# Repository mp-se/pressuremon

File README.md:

# Pressure Monitor for Beer Brewing

PressureMon is a device for measuring pressure in storage or during fermentation.  

It supports ESP32s2 mini, ESP32s3 mini, ESP32c3 mini, ESP32c3 pico and pico and I2C compatible pressure sensors, currently the brand XIDIBEI is supported which has a good range of encapsulated sensors.

Flashing can be done using https://www.gravitymon.com/flasher/index.html which also will help with wifi setup.

Documentation and flashing instructions are available on the [GravityMon PressureMon project page](https://gravitymon.com/project-pressuremon.html)

PCB design is located [here](https://github.com/mp-se/pcb-designs/) 

3D models for a case can be found in the 3d directory on github.

If you want to support my work you can do that through these options

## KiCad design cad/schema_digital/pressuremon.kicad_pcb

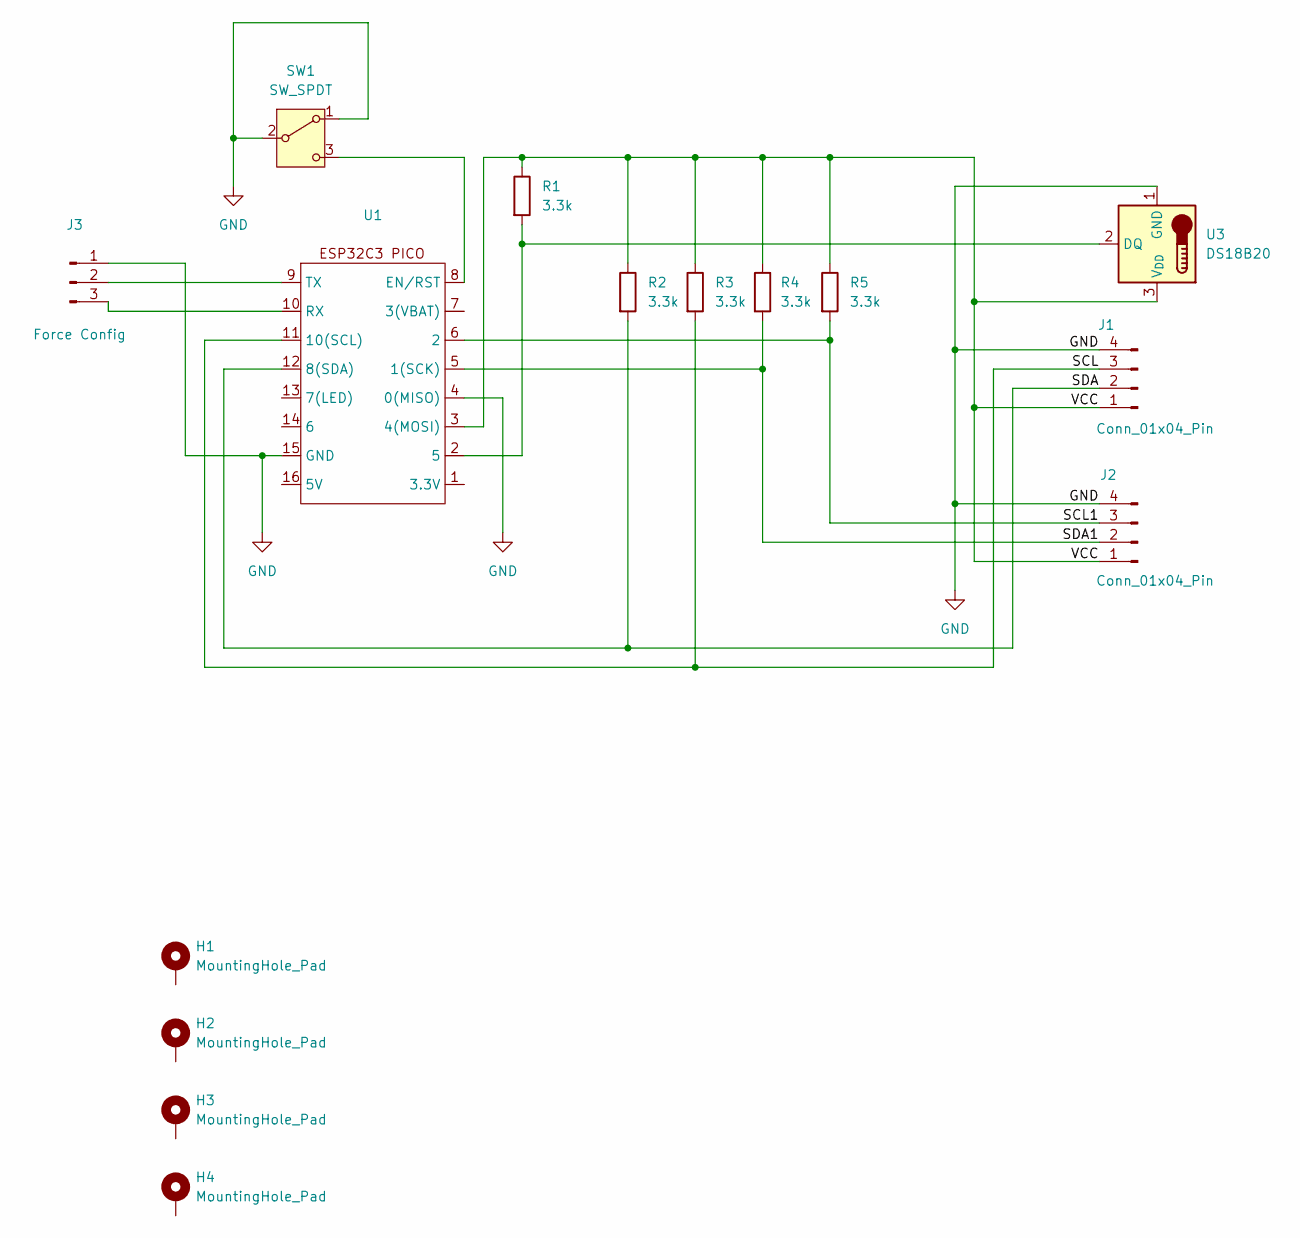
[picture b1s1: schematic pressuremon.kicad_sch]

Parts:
H1, H2, H3, H4: MountingHole_Pad; MountingHole_2.2mm_M2_ISO7380_Pad
J1, J2: Conn_01x04_Pin; PinHeader_1x04_P2.54mm_Vertical
J3: Force Config; PinHeader_1x03_P2.54mm_Vertical
R1, R2, R3, R4, R5: 3.3k; R_Axial_DIN0204_L3.6mm_D1.6mm_P7.62mm_Horizontal
SW1: SW_SPDT; PinHeader_1x03_P2.54mm_Vertical
U1: ESP32C3-pico
U3: DS18B20; TO-92L_Inline_Wide

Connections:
/SCL: J1.3, R3.2, U1.11 (10(SCL))
/SCL1: J2.3, R5.2, U1.6 (2)
/SDA: J1.2, R2.2, U1.12 (8(SDA))
/SDA1: J2.2, R4.2, U1.5 (1(SCK))
/VCC: J1.1, J2.1, R1.1, R2.1, R3.1, R4.1, R5.1, U1.3 (4(MOSI)), U3.3 (V_{DD})
GND: J1.4, J2.4, J3.1, SW1.1 (A), SW1.2 (B), U1.4 (0(MISO)), U1.15 (GND), U3.1 (GND)
unnamed: J3.2, U1.9 (TX)
unnamed: J3.3, U1.10 (RX)
unnamed: SW1.3 (C), U1.8 (EN/RST)
unnamed: R1.2, U1.2 (5), U3.2 (DQ)

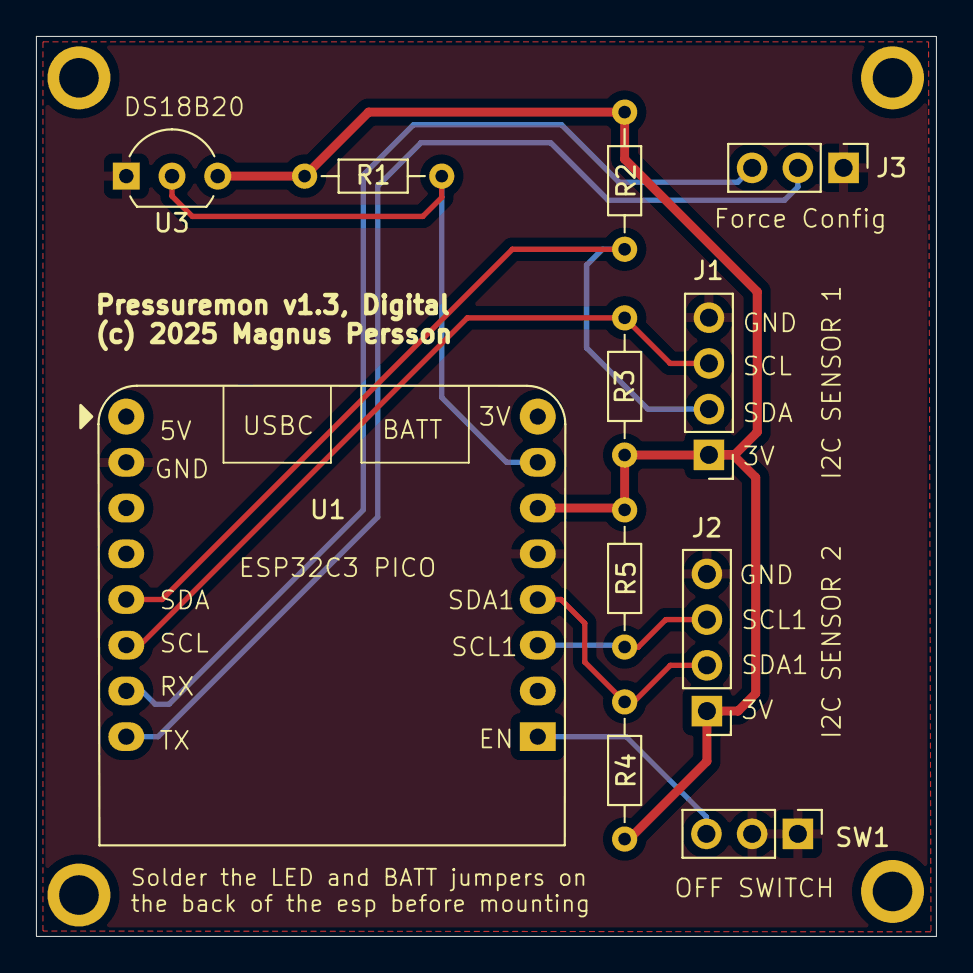
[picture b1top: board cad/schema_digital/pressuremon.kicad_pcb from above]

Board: 2 copper layers, 50.0 x 50.0 mm, 15 parts (0 on the bottom side), 10 nets.

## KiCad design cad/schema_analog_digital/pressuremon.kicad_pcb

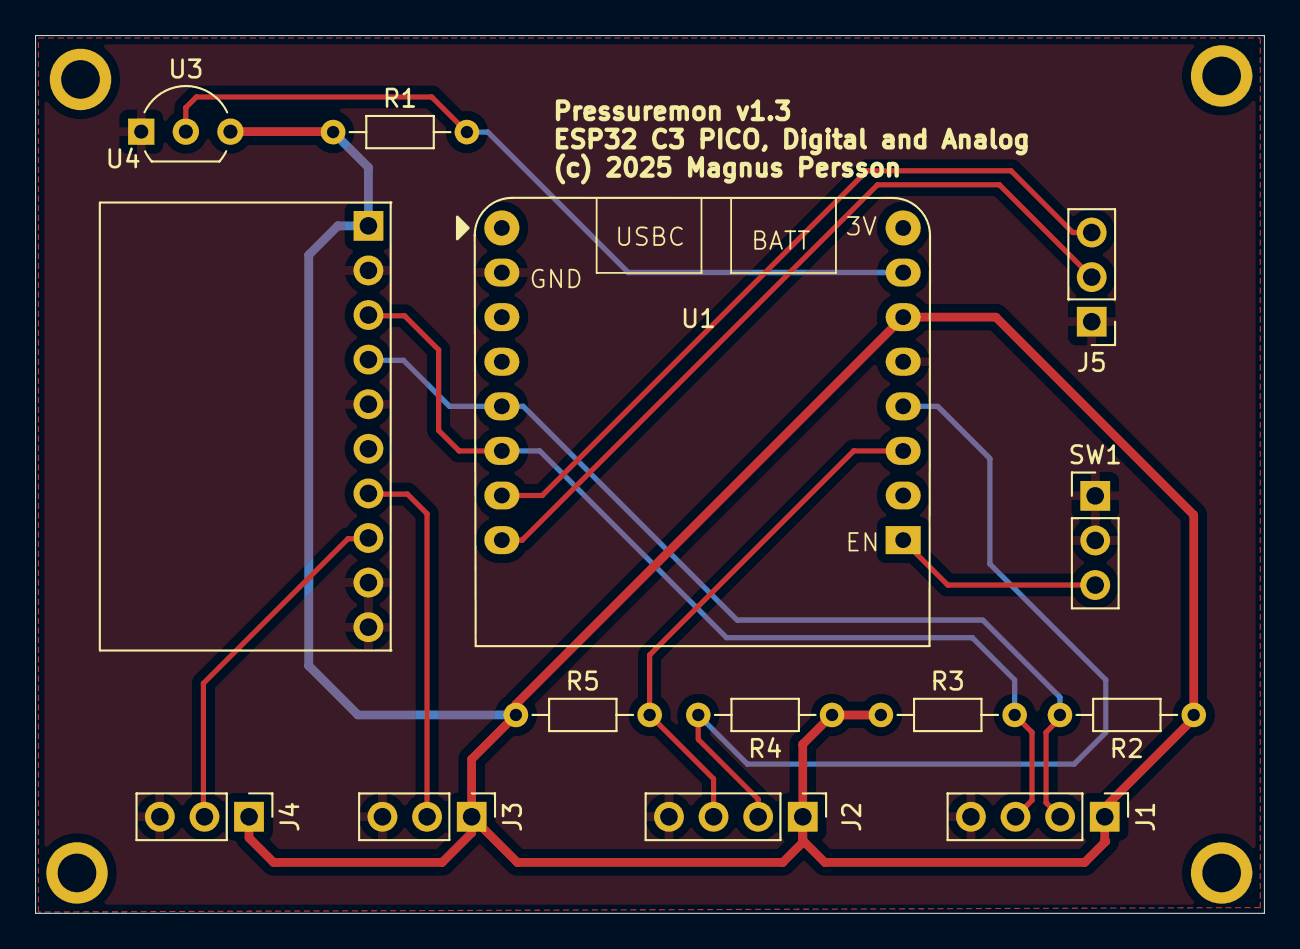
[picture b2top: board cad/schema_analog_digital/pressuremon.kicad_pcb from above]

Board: 2 copper layers, 70.0 x 50.0 mm, 18 parts (0 on the bottom side), 12 nets.

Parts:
H1, H2, H3, H4: MountingHole_Pad; MountingHole_2.2mm_M2_ISO7380_Pad
J1: Digital Pressure 1; PinHeader_1x04_P2.54mm_Vertical
J2: Digital Pressure 2; PinHeader_1x04_P2.54mm_Vertical
J3: Analog Pressure 1; PinHeader_1x03_P2.54mm_Vertical
J4: Analog Pressure 2; PinHeader_1x03_P2.54mm_Vertical
J5: Conn_01x03_Pin; PinHeader_1x03_P2.54mm_Vertical
R1, R2, R3, R4, R5: 3.3k; R_Axial_DIN0204_L3.6mm_D1.6mm_P7.62mm_Horizontal
SW1: SW_DPDT_x2; PinHeader_1x03_P2.54mm_Vertical
U1: ESP32C3-pico
U3: DS18B20; TO-92L_Inline_Wide
U4: ads1115

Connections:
/DATA: J3.2, U4.7 (A0)
/DATA1: J4.2, U4.8 (A1)
/SCL: J1.3, R3.2, U1.11 (10(SCL)), U4.3 (SCL)
/SCL1: J2.3, R5.2, U1.6 (2)
/SDA: J1.2, R2.2, U1.12 (8(SDA)), U4.4 (SDA)
/SDA1: J2.2, R4.2, U1.5 (1(SCK))
/VCC: J1.1, J2.1, J3.1, J4.1, R1.1, R2.1, R3.1, R4.1, R5.1, U1.3 (4(MOSI)), U3.3 (V_{DD}), U4.1 (VDD)
GND: J1.4, J2.4, J3.3, J4.3, J5.1, SW1.1 (A), SW1.2 (B), U1.4 (0(MISO)), U1.15 (GND), U3.1 (GND), U4.2 (GND), U4.5 (ADDR), U4.9 (A2), U4.10 (A3)
unnamed: J5.2, U1.9 (TX)
unnamed: J5.3, U1.10 (RX)
unnamed: SW1.3 (C), U1.8 (EN/RST)
unnamed: R1.2, U1.2 (5), U3.2 (DQ)

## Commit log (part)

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2021-02-23 Initial version, not fully tested
2021-02-24 Added testcases for api
2021-02-25 Added id checks for reset/wifi
2021-02-25 Created pcb
2021-02-25 new version baseline 0.2
2021-02-25 Version file
2021-02-28 Change sleep mode + added web debug option
2021-03-11 Added pressure sensor settings to status
2021-03-11 Moved pressure sensor status to debug
2021-03-11 Added headers to post requests, fixed BF
2021-03-12 Build 0.2.1
2021-03-28 Removed LED
2021-03-28 Copy files to /bin after build
2021-03-28 Updated config för DRD
2021-03-29 Added UI and refactor API's
2021-03-29 fixed 2 bugs
2021-03-30 New test build
2021-03-30 Deleted file
2021-04-01 Swapped wifimanager and tested drd
2023-11-05 Refactor for espframework and esp32
2023-11-05 Fix UI errors
2024-08-12 Update build deps
2024-08-12 Remove 32 binaries
2024-08-12 Remove old html files
2024-08-12 Add build scripts
2024-08-12 Refactor code to match new espframework
2024-08-12 Added example ui files
2024-08-12 Remove old test files
2024-08-12 Add s2 binaries
2024-08-13 Update pressure unit tags
2024-08-13 Upd gitignore
2024-08-14 Update version
2024-08-14 Update licence
2024-08-14 Refactor code to match esp fwk 1.0
2024-08-14 Update sensor defintions
2024-08-14 Updates connected to presssure sensors
2024-08-14 Added dependant as lib
2024-08-14 Added UI build
2024-08-14 Change pressure key
2024-08-14 Fixed temp in status
2024-08-14 Add build
2024-08-14 Fixed formatting for data
2024-08-14 GitHub Action Build
2024-10-14 Refactor and add support for new pressure sensor
2024-10-15 Fix status flag
2024-10-15 Migrate to espfwk 1.1
2025-01-10 Refactor code, add xidibei sensor support, prepare for merge with gravitymon project for one common codebase
2025-01-10 Adding i2c scanner
2025-01-10 Remove build workflow
2025-01-10 Adding datascheets for XDB401
2025-01-11 Adding multiplexer support
2025-01-12 Update schmatic and moved specification to own folder
2025-01-12 Tested sensor drivers and added optional schematics
2025-01-13 Cleanup and focus on xidibei sensors for first release
2025-01-22 Adding analog sensor support via external ADC
2025-01-22 Remove unused code
2025-01-23 Adding voltage method for sensor classes
2025-01-25 Adding new target and 0.2hpa sensor
2025-01-26 Update code to work with i2c sensor
2025-01-27 Remove unused script
2025-01-28 Update code to align with gravitymon implementation
2025-01-29 Align with gravitymon
2025-01-29 Adding validation of min/max pressure
2025-01-29 Update logging levels, fixed conversion of negative pressure
2025-01-30 update code
2025-01-30 Update action
2025-01-30 Update build
2025-01-30 Adding bins
2025-01-30 Adding readme
2025-01-30 Added flash bin for s3
2025-01-30 Adding flash script
2025-01-30 Update html
2025-01-30 Limit validation to max pressure
2025-01-31 Update workflow
2025-01-31 Force build
2025-01-31 Adding additional targets
2025-01-31 Adding more targets
2025-01-31 Adding flash files for c3 and s2
2025-02-06 Update build scripts
2025-02-14 Update build process
2025-03-12 Adding 2 pcb options
2025-03-28 Update build script
2025-03-29 Update pcb for digital sensors
2025-03-29 Update pcb
2025-04-07 Refactor and move function to pressure files
2025-04-07 Initial commit on orphan branch
2025-04-08 Adding documentation
2025-04-09 Update dependency
2025-04-09 Update documentation
2025-04-14 Sync with gravmon repo
2025-04-14 Adding new partition file
2025-04-14 Update partition setup
2025-04-20 Updating schematic, adding off switch
2025-04-20 Updating docs
2025-04-20 Adding off switch
2025-04-25 Update build instructions for the hardware
2025-04-27 Adding mounting holes to pcb
2025-04-27 Update analog pcb
2025-05-07 Update readme and move schema
2025-05-11 Move code from gravitymon project
2025-05-11 Update dependecies + precommit
2025-05-15 Fix issue with tempsensor crashing
2025-05-16 Using battery percentage with battery type
2025-05-23 Fixed force config feature
2025-05-23 Update to release
2025-05-24 Adding define to enable second sensor
2025-05-24 Adding driver for OLED display
2025-05-25 Added message when display not found
2025-05-25 Bump version, enable sensor 2
2025-05-25 Update display output
2025-05-25 Adding support for custom analog sensors
2025-05-25 Update flasher link
2025-05-25 Switch to kpa for custom analog
2025-05-26 Enable i2c scanning of second bus
2025-05-28 Fix link to flasher
2025-05-28 Update code for second i2c bus.
2025-05-29 Adding SoftWire for second i2c bus on boards with one hardware controller
2025-06-08 Remove debug prints
2025-06-08 FIxed temperature on display
2025-06-08 Update docs
2025-06-09 Build beta 1
2025-06-15 Fixed LED on pico board
2025-06-15 Update push test api
2025-06-15 Bump version
2025-06-25 Update dependencies
2025-08-05 Update deps and increase stack for webserver
2025-09-09 Rename bin and add feature api
2025-09-09 Update deps
2025-09-10 Update bin names
2025-09-27 Adding support for Arduino 3.x
2025-09-27 Downgrade to 6.11
2025-09-27 Remove 8266 deps
2025-10-01 Optimzie build and fix potential issues
2025-10-03 Fiorce build
2025-10-12 Adding script to copy ui files
2025-10-18 Fix deps
2025-10-18 Fix battery reading setup
2025-12-25 Adding temp value to loop serial output
2025-12-28 Revered to arduino 2.x for smaller size
2025-12-28 Update fileviewer
2025-12-28 Added 3d model
2025-12-28 Update release notes
2026-04-09 Switch to dual license

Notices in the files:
cad/schema_analog_digital/pressuremon.kicad_pcb:
(c) 2025 Magnus Persson
